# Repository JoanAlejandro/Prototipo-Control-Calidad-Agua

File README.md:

# Prototipo Control Calidad Del Agua
En este repositorio se encuentra toda la documentación del desarrollo del proyecto "Prototipo Control Calidad Del Agua" desarrollado por estudiantes de primer semestre del pregrado en Ingeniería Electrónica de la Universidad Nacional de Colombia para la asignatura de Taller de electrónica.

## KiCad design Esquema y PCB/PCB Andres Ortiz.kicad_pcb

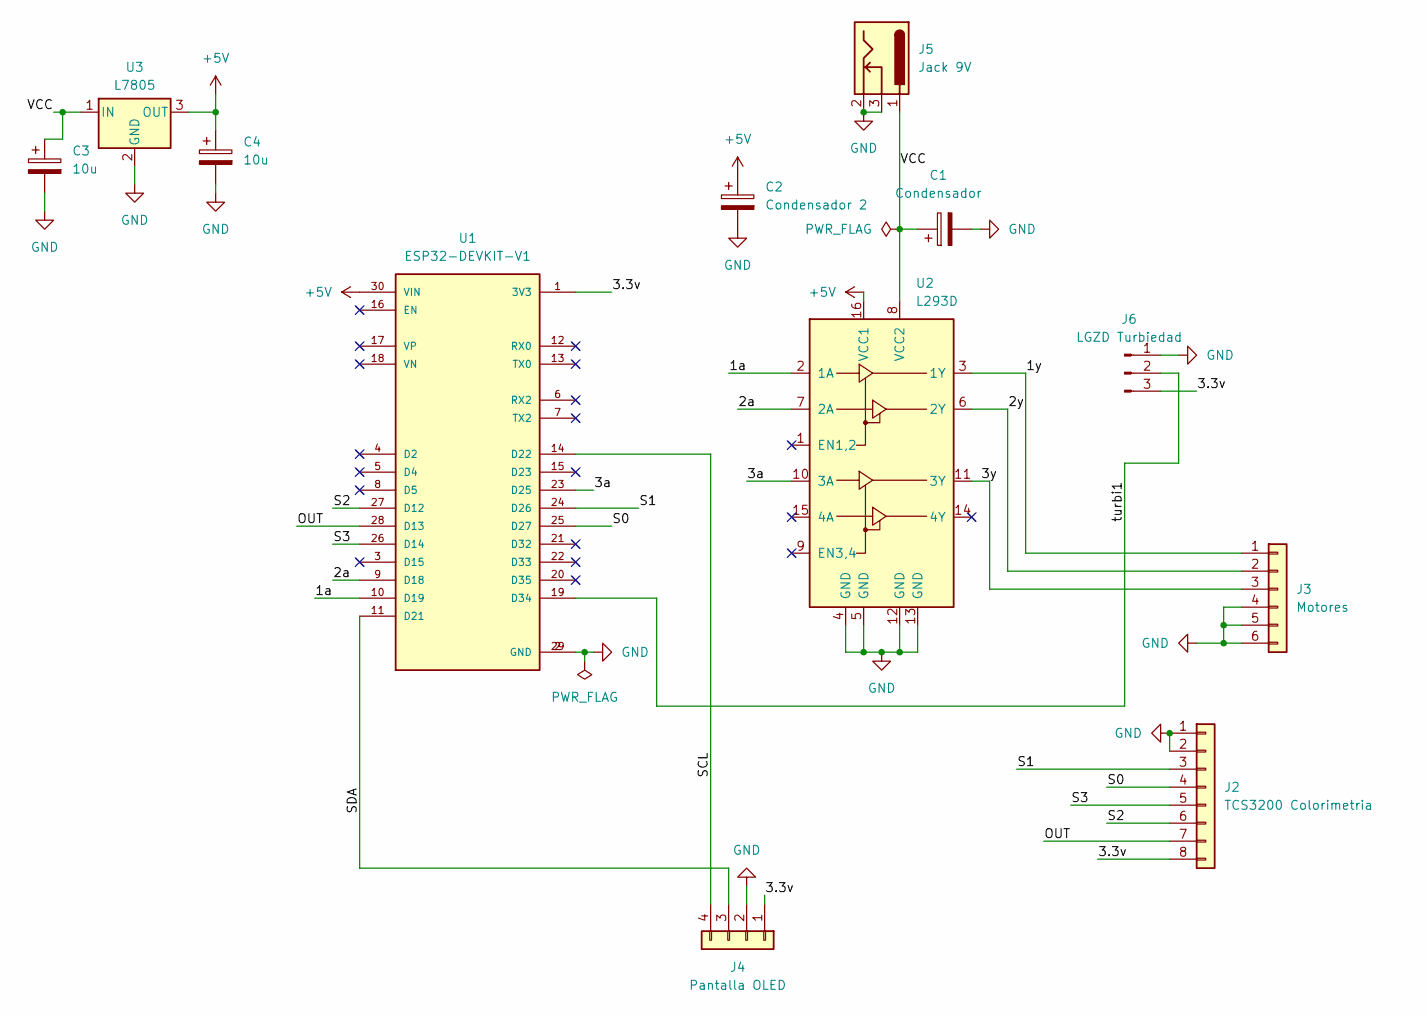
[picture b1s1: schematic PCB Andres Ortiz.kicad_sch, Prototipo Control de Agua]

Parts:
C1: Condensador; CP_Radial_D5.0mm_P2.00mm
C2: Condensador 2; CP_Radial_D5.0mm_P2.00mm
C3, C4: 10u; CP_Radial_D5.0mm_P2.00mm
J2: TCS3200 Colorimetria; TerminalBlock_bornier-8_P5.08mm
J3: Motores; TerminalBlock_bornier-6_P5.08mm
J4: Pantalla OLED; TerminalBlock_bornier-4_P5.08mm
J5: Jack 9V; BarrelJack_Horizontal
J6: LGZD Turbiedad; TerminalBlock_bornier-3_P5.08mm
U1: ESP32-DEVKIT-V1; ESP32-C3-DevKitM-1; PARTREV N/A
U2: L293D; DIP-16_W7.62mm
U3: L7805; TO-220-3_Vertical

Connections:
+5V: C2.1, C4.1, U1.30 (VIN), U2.16 (VCC1), U3.3 (OUT)
/1a: U1.10 (D19), U2.2 (1A)
/1y: J3.1, U2.3 (1Y)
/2a: U1.9 (D18), U2.7 (2A)
/2y: J3.2, U2.6 (2Y)
/3.3v: J2.8, J4.1, J6.3, U1.1 (3V3)
/3a: U1.23 (D25), U2.10 (3A)
/3y: J3.3, U2.11 (3Y)
/OUT: J2.7, U1.28 (D13)
/S0: J2.4, U1.25 (D27)
/S1: J2.3, U1.24 (D26)
/S2: J2.6, U1.27 (D12)
/S3: J2.5, U1.26 (D14)
/SCL: J4.4, U1.14 (D22)
/SDA: J4.3, U1.11 (D21)
/VCC: C1.1, C3.1, J5.1, U2.8 (VCC2), U3.1 (IN)
/turbi1: J6.2, U1.19 (D34)
GND: C1.2, C2.2, C3.2, C4.2, J2.1, J2.2, J3.4, J3.5, J3.6, J4.2, J5.2, J5.3, J6.1, U1.2 (GND), U1.29 (GND), U2.4 (GND), U2.5 (GND), U2.12 (GND), U2.13 (GND), U3.2 (GND)

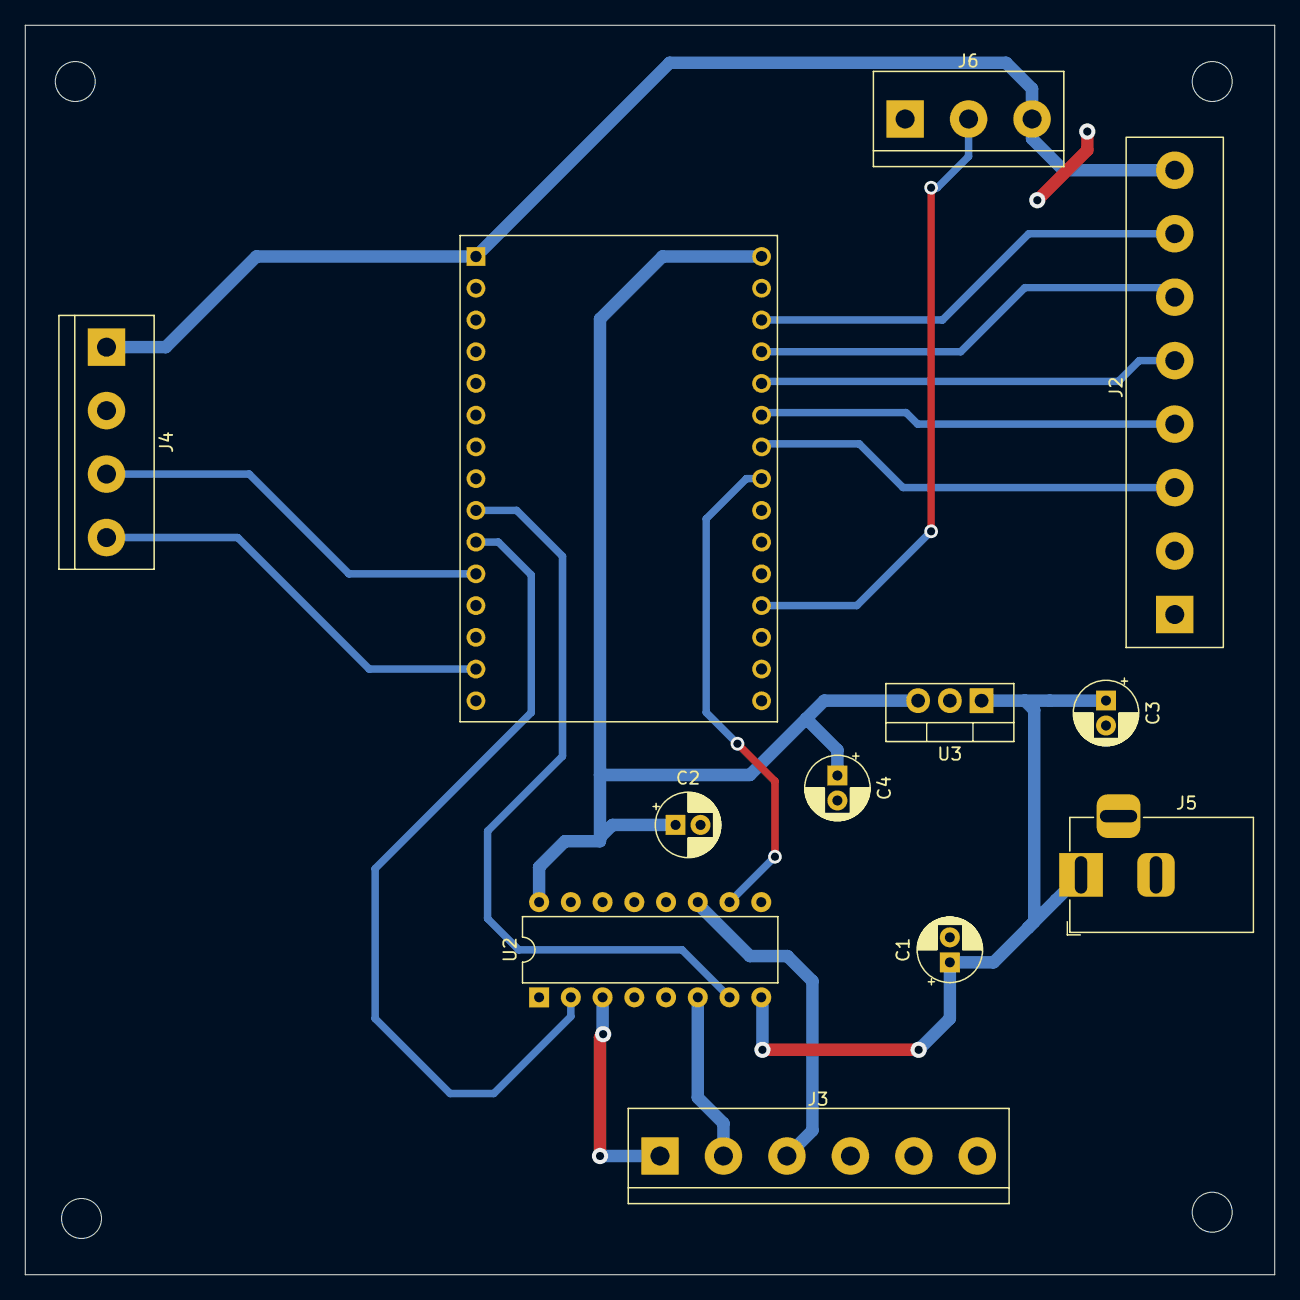
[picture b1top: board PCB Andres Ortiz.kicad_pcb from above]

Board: 2 copper layers, 100.0 x 100.0 mm, 12 parts (0 on the bottom side), 18 nets.

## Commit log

2025-03-05 Actualización del readme
2025-03-06 README.md
2025-03-08 Create VIdeos
2025-03-08 Create VIDEO-PRESENTACION
